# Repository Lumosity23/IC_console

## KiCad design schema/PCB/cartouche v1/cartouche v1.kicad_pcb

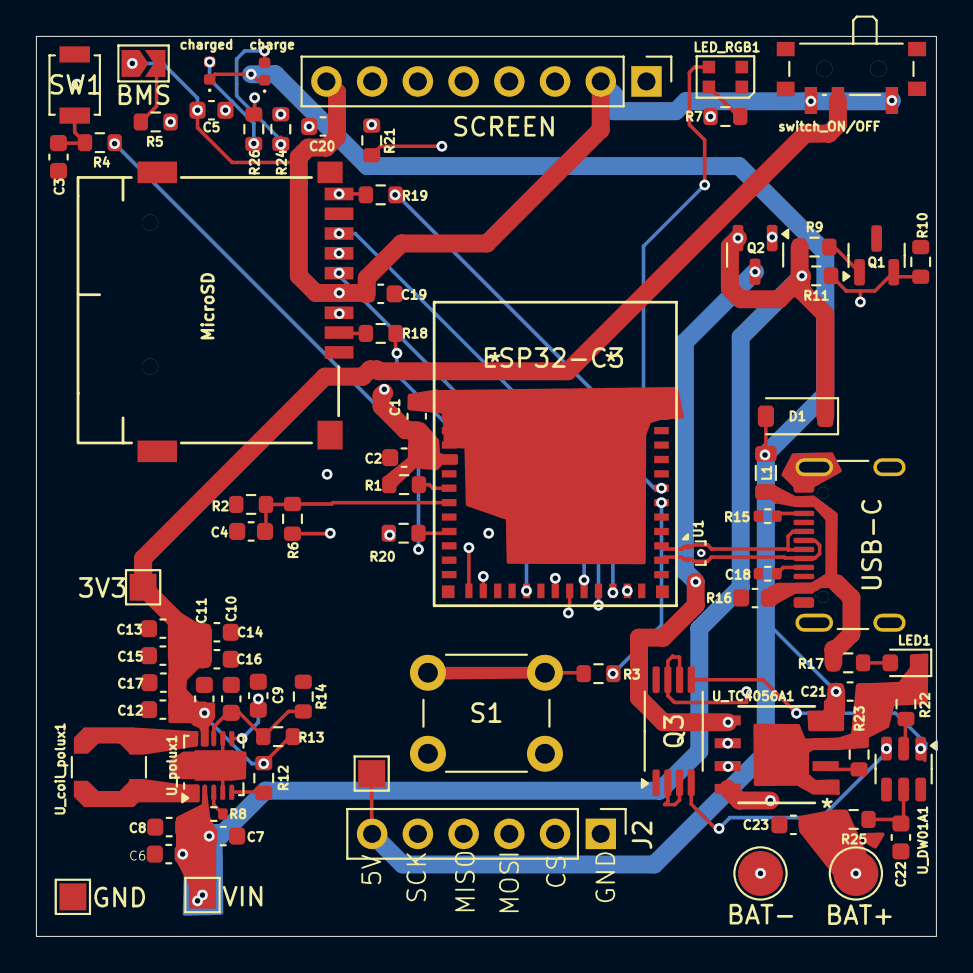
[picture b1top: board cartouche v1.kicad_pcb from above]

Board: 4 copper layers, 50.0 x 50.0 mm, 78 parts (0 on the bottom side), 51 nets.

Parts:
3V3: VOUT3v3; TestPoint_Pad_1.5x1.5mm
5V+1: 5V+; TestPoint_Pad_1.5x1.5mm
BAT+: BAT+; TestPoint_Pad_D2.5mm
BAT-: BAT-; TestPoint_Pad_D2.5mm
BMS: SolderJumper_2_Open; SolderJumper-2_P1.3mm_Open_TrianglePad1.0x1.5mm
C1, C4, C5, C8, C9, C11, C19, C20, C21, C22: 100nF; C_0603_1608Metric
C2, C3: 1uF; C_0603_1608Metric
C6, C7, C12, C13, C14, C15, C16, C17, C18, C23: 10uF; C_0603_1608Metric
C10: 2.2pF; C_0603_1608Metric
D1: 1N5819/SOD-123; D_SOD-123
ESP32-C3: ESP32-C3-MINI-1-N4; ESP32-C3-MINI-1_EXP
GND: GND; TestPoint_Pad_1.5x1.5mm
J2: Conn_01x06; PinHeader_1x06_P2.54mm_Vertical
L1: 60Ω; L_0805_2012Metric
LED1: LED0603; LED_0603_1608Metric
LED_RGB1: WS2812B-2020; LED_WS2812B-2020_PLCC4_2.0x2.0mm
MicroSD: MICRO SD卡座; J_SD_Card-micro_socket_A
Q1, Q2: AO3401A_C700954; SOT-23
Q3: WA-FS8205A; TSSOP-8_4.4x3mm_P0.65mm
R1, R3, R4, R9, R10, R18, R19, R20, R21: 10kΩ; R_0603_1608Metric
R2, R6, R11, R12: 100kΩ; R_0603_1608Metric
R5: 10k; R_0603_1608Metric
R7, R17: 330Ω; R_0603_1608Metric
R8: 100kΩ; R_0402_1005Metric
R13: 360kΩ; R_0603_1608Metric
R14: 64.9kΩ; R_0603_1608Metric
R15, R16: 5.1kΩ; R_0402_1005Metric
R22, R24, R26: 1kΩ; R_0603_1608Metric
R23: 3kΩ; R_0603_1608Metric
R25: 100Ω; R_0603_1608Metric
S1: Silicone Button 8x8x5mm; SW_PUSH_6mm_H4.3mm
SCREEN: tft1.14; PinHeader_1x08_P2.54mm_Vertical
SW1: SW_RESET; SW_SPST_B3U-1000P
U1: TPD2EUSB30; Texas_DRT-3
USB-C: USB_C_Receptacle_USB2.0_16P; USB_C_Receptacle_GCT_USB4105-xx-A_16P_TopMnt_Horizontal
U_DW01A1: DW01A; SOT-23-6
U_TC4056A1: TC4056A.; TC4056A
U_coil_polux1: 1.2uH; L_Coilcraft_LPS4018
U_polux1: TPS63060DSCR; Texas_S-PWSON-N10
VIN: Vin; TestPoint_Pad_1.5x1.5mm
charge: YLED0402R; LED_0402_1005Metric
charged: YLED0402G; LED_0402_1005Metric
switch_ON/OFF: MSK-11027 Toggle Switches; SW_SPDT_PCM12

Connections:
3v3: 3V3.1, C11.2, C12.2, C13.2, C14.2, C15.2, C16.2, C17.2, R12.1, R13.2, U_polux1.9 (VOUT), switch_ON/OFF.2
+5V: 5V+1.1, C21.1, D1.2 (A), J2.6, L1.2, U_TC4056A1.4 (VCC), U_TC4056A1.8 (CE), charge.1 (A), charged.1 (A)
Boot Mode Select: ESP32-C3.23 (IO9), R5.1
CD: ESP32-C3.22 (IO8), R19.1
CS Console: ESP32-C3.18 (IO4), J2.2
CS Écran: ESP32-C3.13 (IO1), R21.1
CS_sdcard: ESP32-C3.16 (IO10), R18.2
D+: ESP32-C3.27 (IO19), U1.1 (D+), USB-C.A6 (D+), USB-C.B6 (D+)
D-: ESP32-C3.26 (IO18), U1.2 (D-), USB-C.A7 (D-), USB-C.B7 (D-)
GND: BAT-.1, C1.1, C2.1, C3.2, C4.2, C5.1, C6.1, C7.1, C8.1, C9.2, C10.1, C11.1, C12.1, C13.1, C14.1, C15.1, C16.1, C17.1, C18.1, C19.2, C20.1, C21.2, C22.1, C23.1, ESP32-C3.1 (GND), ESP32-C3.2 (GND), ESP32-C3.11 (GND), ESP32-C3.14 (GND), ESP32-C3.36 (GND), ESP32-C3.37 (GND), ESP32-C3.38 (GND), ESP32-C3.39 (GND), ESP32-C3.40 (GND), ESP32-C3.41 (GND), ESP32-C3.42 (GND), ESP32-C3.43 (GND), ESP32-C3.44 (GND), ESP32-C3.45 (GND), ESP32-C3.46 (GND), ESP32-C3.47 (GND), ESP32-C3.48 (GND), ESP32-C3.49 (GND), ESP32-C3.50 (GND), ESP32-C3.51 (GND), ESP32-C3.52 (GND), ESP32-C3.53 (GND), GND.1, J2.1, LED1.1 (-), LED_RGB1.2 (GND), MicroSD.6, MicroSD.SH, Q1.3 (D), Q3.2 (S1), Q3.3 (S1), Q3.6 (S2), Q3.7 (S2), R2.1, R10.1, R14.1, R15.1, R16.2, R22.2, R23.1, S1.2, SCREEN.1 (GND), SW1.1, U1.3 (GND), USB-C.A1 (GND), USB-C.A12 (GND), USB-C.B1 (GND), USB-C.B12 (GND), USB-C.S1 (SHIELD), U_DW01A1.6 (GND), U_TC4056A1.1 (TEMP), U_TC4056A1.3 (GND), U_polux1.4 (PS/SYNC), U_polux1.7 (GND), U_polux1.11 (PAD)
GPIO2: ESP32-C3.5 (IO2), R1.2
LEDrgb: ESP32-C3.31 (TXD0), LED_RGB1.3 (DI)
unnamed: BMS.2 (B), R5.2
unnamed: C3.1, R4.2, SW1.2
unnamed: C18.2, L1.1, R17.1, USB-C.A4 (VBUS), USB-C.A9 (VBUS), USB-C.B4 (VBUS), USB-C.B9 (VBUS)
unnamed: R16.1, USB-C.A5 (CC1)
unnamed: R15.2, USB-C.B5 (CC2)
unnamed: LED1.2 (+), R17.2
unnamed: R24.2, charge.2 (K)
unnamed: R26.2, charged.2 (K)
unnamed: LED_RGB1.4 (VDD), R7.2
unnamed: Q1.1 (G), R9.2
unnamed: Q1.2 (S), Q2.1 (G), R10.2, R11.2
unnamed: Q3.4 (G1), U_DW01A1.3 (OC)
unnamed: Q3.5 (G2), U_DW01A1.1 (OD)
unnamed: R3.2, S1.1
unnamed: MicroSD.2, R18.1
unnamed: MicroSD.9 (CD), R19.2
unnamed: R21.2, SCREEN.7 (CS)
unnamed: R20.2, SCREEN.5 (RES)
unnamed: R22.1, U_DW01A1.2 (VM)
unnamed: R24.1, U_TC4056A1.7 (CHRG)
unnamed: R23.2, U_TC4056A1.2 (PROG)
unnamed: R26.1, U_TC4056A1.6 (STDBY)
unnamed: R8.2, U_polux1.3 (EN)
unnamed: C10.2, R13.1, R14.2, U_polux1.8 (FB)
unnamed: U_coil_polux1.1, U_polux1.1 (L1)
unnamed: U_coil_polux1.2, U_polux1.10 (L2)
unnamed: R12.2, U_polux1.5 (PG)
unnamed: C9.1, U_polux1.6 (VAUX)
OUT+: BAT+.1, C23.2, Q2.3 (D), R6.2, R25.1, U_TC4056A1.5 (BAT)
SPI MISO: ESP32-C3.21 (IO7), J2.4, MicroSD.7
SPI MOSI: ESP32-C3.19 (IO5), J2.3, MicroSD.3, SCREEN.4 (SDA)
SPI SCK: ESP32-C3.20 (IO6), J2.5, MicroSD.5, SCREEN.3 (SCL)
SW-1: ESP32-C3.30 (RXD0), R3.1
SW-reset: ESP32-C3.8 (EN), R4.1, R20.1
TENSION: C4.1, ESP32-C3.6 (IO3), R2.2, R6.1
VCCfhd: C22.2, R25.2, U_DW01A1.5 (VCC)
Vin: C6.2, C7.2, C8.2, D1.1 (C), Q2.2 (S), R8.1, R9.1, R11.1, U_polux1.2 (VIN), VIN.1
Vout3v3: BMS.1 (A), C1.2, C2.2, C5.2, C19.1, C20.2, ESP32-C3.3 (3V3), MicroSD.4, R1.1, R7.1, SCREEN.2 (VCC), SCREEN.8 (BLK), switch_ON/OFF.1, switch_ON/OFF.3
Écran D/C: ESP32-C3.12 (IO0), SCREEN.6 (DC)

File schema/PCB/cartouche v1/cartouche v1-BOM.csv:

"Id";"Designator";"Footprint";"Quantity";"Designation";"Supplier and ref";
1;"5V+1";"TestPoint_Pad_1.5x1.5mm";1;"5V+";;;
2;"R4,R21,R10,R18,R19,R3,R1,R20,R9";"R_0603_1608Metric";9;"10kΩ";;;
3;"R13";"R_0603_1608Metric";1;"360kΩ";;;
4;"R24,R26,R22";"R_0603_1608Metric";3;"1kΩ";;;
5;"R16,R15";"R_0402_1005Metric";2;"5.1kΩ";;;
6;"U1";"Texas_DRT-3";1;"TPD2EUSB30";;;
7;"C4,C11,C8,C1,C22,C5,C19,C20,C9,C21";"C_0603_1608Metric";10;"100nF";;;
8;"C18,C12,C15,C16,C7,C6,C13,C23,C14,C17";"C_0603_1608Metric";10;"10uF";;;
9;"GND";"TestPoint_Pad_1.5x1.5mm";1;"GND";;;
10;"U_polux1";"Texas_S-PWSON-N10";1;"TPS63060DSCR";;;
11;"switch_ON/OFF";"SW_SPDT_PCM12";1;"MSK-11027 Toggle Switches";;;
12;"S1";"SW_PUSH_6mm_H4.3mm";1;"Silicone Button 8x8x5mm";;;
13;"LED_RGB1";"LED_WS2812B-2020_PLCC4_2.0x2.0mm";1;"WS2812B-2020";;;
14;"D1";"D_SOD-123";1;"1N5819/SOD-123";;;
15;"U_coil_polux1";"L_Coilcraft_LPS4018";1;"1.2uH";;;
16;"Q1,Q2";"SOT-23";2;"AO3401A_C700954";;;
17;"R14";"R_0603_1608Metric";1;"64.9kΩ";;;
18;"SW1";"SW_SPST_B3U-1000P";1;"SW_RESET";;;
19;"R6,R11,R2,R12";"R_0603_1608Metric";4;"100kΩ";;;
20;"charge";"LED_0402_1005Metric";1;"YLED0402R";;;
21;"C3,C2";"C_0603_1608Metric";2;"1uF";;;
22;"L1";"L_0805_2012Metric";1;"60Ω";;;
23;"VIN";"TestPoint_Pad_1.5x1.5mm";1;"Vin";;;
24;"C10";"C_0603_1608Metric";1;"2.2pF";;;
25;"MicroSD";"J_SD_Card-micro_socket_A";1;"MICRO SD卡座";;;
26;"SCREEN";"PinHeader_1x08_P2.54mm_Vertical";1;"tft1.14";;;
27;"R23";"R_0603_1608Metric";1;"3kΩ";;;
28;"U_TC4056A1";"TC4056A";1;"TC4056A.";;;
29;"R5";"R_0603_1608Metric";1;"10k";;;
30;"J2";"PinHeader_1x06_P2.54mm_Vertical";1;"Conn_01x06";;;
31;"U_DW01A1";"SOT-23-6";1;"DW01A";;;
32;"R8";"R_0402_1005Metric";1;"100kΩ";;;
33;"USB-C";"USB_C_Receptacle_GCT_USB4105-xx-A_16P_TopMnt_Horizontal";1;"USB_C_Receptacle_USB2.0_16P";;;
34;"R7,R17";"R_0603_1608Metric";2;"330Ω";;;
35;"ESP32-C3";"ESP32-C3-MINI-1_EXP";1;"ESP32-C3-MINI-1-N4";;;
36;"Q3";"TSSOP-8_4.4x3mm_P0.65mm";1;"WA-FS8205A";;;
37;"R25";"R_0603_1608Metric";1;"100Ω";;;
38;"3V3";"TestPoint_Pad_1.5x1.5mm";1;"VOUT3v3";;;
39;"BAT-";"TestPoint_Pad_D2.5mm";1;"BAT-";;;
40;"BAT+";"TestPoint_Pad_D2.5mm";1;"BAT+";;;
41;"charged";"LED_0402_1005Metric";1;"YLED0402G";;;
42;"LED1";"LED_0603_1608Metric";1;"LED0603";;;

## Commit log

2025-08-23 add BASE.md
2025-08-23 add .gitignore
2025-08-23 changes something with README
2025-08-23 ajout d'un dossier datasheet
2025-09-18 feat: Add hardware schematics and update project structure
    - Add hardware schematics and PCB layout screenshots to the root README.
    - Update .gitignore to exclude more files.
    - Remove files that should be ignored from git tracking.
    - Add new `code` and `schema/PCB` directories.
    - Remove `BOM_manager` and old `console_symbiote` schema files.
2025-09-18 ajout de schema mermaid
